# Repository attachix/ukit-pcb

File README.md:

## About
This repository contains the files needed to view, modify and manufacture the Printed Circuit Boards(PCB) for the [U:Kit sensor kit](https://github.com/attachix/ukit) project.

.

## PCBs
U:Kit consists currently of 3 PCBS
* [esp-board/](esp-board/) - ESP8266 PCB.
* [base-board/](base-board/) - the main board in the kit
* [smoke-board/](smoke-board) - the board that operates with the smoke sensor

## Hardware Overview
.

## Required Software
For viewing and modifying the PCBs you will need [KiCad](http://kicad-pcb.org/) version 4.0.5 or newer.
In Ubuntu 16.04 you can install it by typing `sudo apt install kicad`.

### Optional Software
If you want to be able to see better the differences between versions you will need
* gerbv - for differences in Gerber files
* [ImageMagick](https://www.imagemagick.org) - for differences in image files
* diffpdf - for differences in PDF files
* eeplot - for differences in Schema files.

## Copyright
Copyright (c) 2016-2018, Slavey Karadzhov <slav@attachix.com>. All rights reserved.

## Authors
* Cviatko Delchev <cviatko@attachix.com> - Our hard-core hardware guru
* Slavey Karadzhov <slav@attachix.com>
* .. Contributors - See https://github.com/attachix/ukit-pcb/graphs/contributors

## License
All files in this repository are licensed under Creative Commons Non-Commercial-Share Alike 3.0 License . See the [LICENSE](LICENSE) file details. Basically it means that

### You are free to
* Share — copy and redistribute the material in any medium or format
* Adapt — remix, transform, and build upon the material

The licensor cannot revoke these freedoms as long as you follow the license terms.

### Under the following terms:
* Attribution — You must give appropriate credit, provide a link to the license, and indicate if changes were made. You may do so in any reasonable manner, but not in any way that suggests the licensor endorses you or your use.

* NonCommercial — You may not use the material for commercial purposes.

No additional restrictions — You may not apply legal terms or technological measures that legally restrict others from doing anything the license permits.

Credit can be attributed through a link to the creator website: https://attachix.com

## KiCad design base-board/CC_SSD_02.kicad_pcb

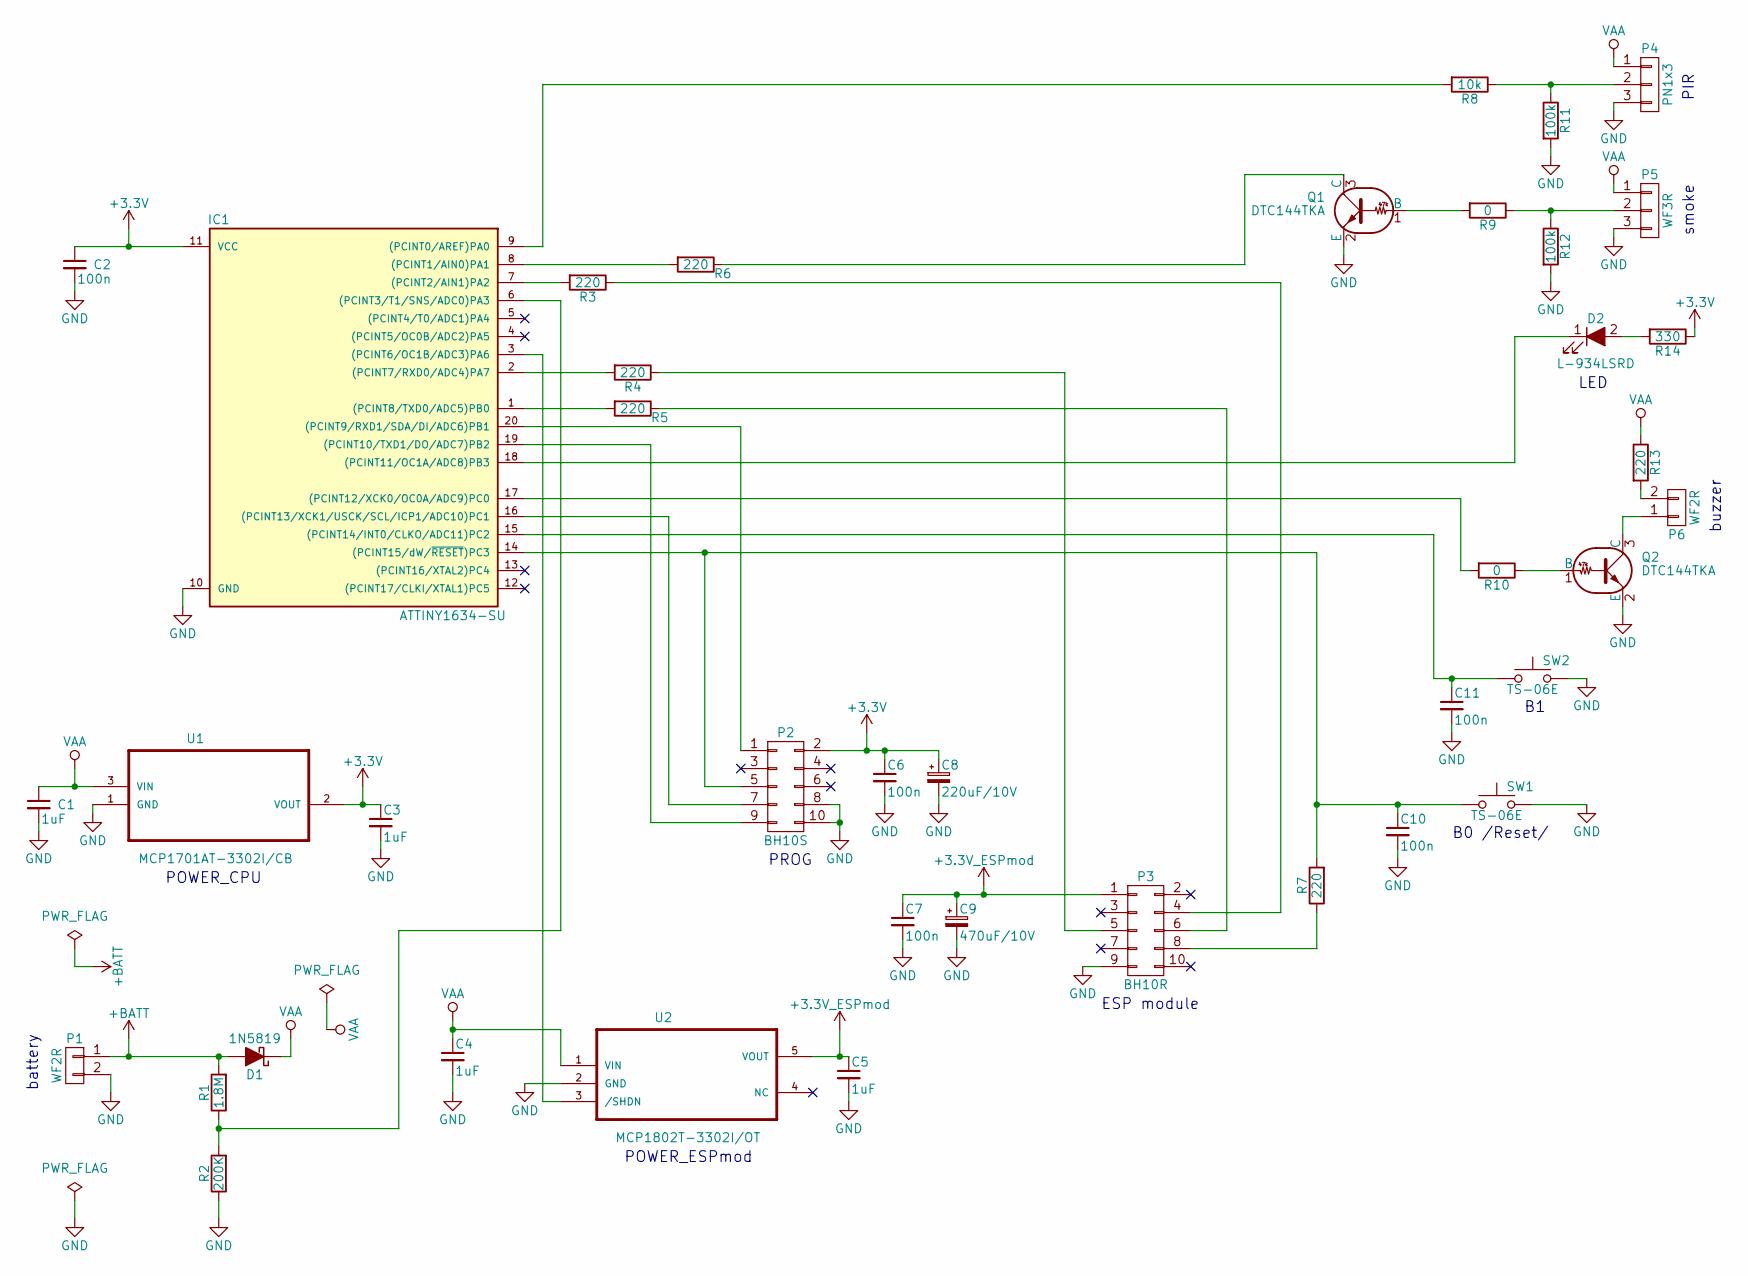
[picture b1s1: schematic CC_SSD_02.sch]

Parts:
C1, C3, C4, C5: 1uF; C_0805_HandSoldering
C2, C6, C7, C10, C11: 100n; C_0805_HandSoldering
C8: 220uF/10V; CP_Radial_D8.0mm_P2.50mm
C9: 470uF/10V; CP_Radial_D8.0mm_P2.50mm
D1: 1N5819; D_SMA_Handsoldering
D2: L-934LSRD; LED_D3.0mm
IC1: ATTINY1634-SU; SOIC-20W_7.5x12.8mm_Pitch1.27mm
P1, P6: WF2R
P2: BH10S; IDC_Header_Straight_10pins
P3: BH10R
P4: PN1x3
P5: WF3R
Q1, Q2: DTC144TKA; SOT-23_Handsoldering
R1: 1.8M; R_0805_HandSoldering
R2: 200K; R_0805_HandSoldering
R3, R4, R5, R6, R7, R13: 220; R_0805_HandSoldering
R8: 10k; R_0805_HandSoldering
R9, R10: 0; R_0805_HandSoldering
R11, R12: 100k; R_0805_HandSoldering
R14: 330; R_0805_HandSoldering
SW1, SW2: TS-06E; SW_PUSH_6mm
U1: MCP1701AT-3302I/CB; SOT-23_Handsoldering
U2: MCP1802T-3302I/OT; SOT-23-5_HandSoldering

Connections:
+3.3V_ESPmod: C5.1, C7.1, C9.1, P3.1, U2.5 (VOUT)
+3V3: C2.1, C3.1, C6.1, C8.1, IC1.11 (VCC), P2.2, R14.1, U1.2 (VOUT)
+BATT: D1.2 (A), P1.1, R1.2
GND: C1.2, C2.2, C3.2, C4.2, C5.2, C6.2, C7.2, C8.2, C9.2, C10.2, C11.2, IC1.10 (GND), P1.2, P2.8, P2.10, P3.9, P4.3, P5.3, Q1.2 (E), Q2.2 (E), R2.1, R11.2, R12.2, SW1.2, SW2.2, U1.1 (GND), U2.2 (GND)
unnamed: C10.1, IC1.14 ((PCINT15/dW/~RESET~)PC3), P2.5, R7.2, SW1.1
unnamed: C11.1, IC1.15 ((PCINT14/INT0/CLKO/ADC11)PC2), SW2.1
unnamed: D2.1 (K), IC1.18 ((PCINT11/OC1A/ADC8)PB3)
unnamed: D2.2 (A), R14.2
unnamed: IC1.1 ((PCINT8/TXD0/ADC5)PB0), R5.2
unnamed: IC1.2 ((PCINT7/RXD0/ADC4)PA7), R4.2
unnamed: IC1.3 ((PCINT6/OC1B/ADC3)PA6), U2.3 (/SHDN)
unnamed: IC1.6 ((PCINT3/T1/SNS/ADC0)PA3), R1.1, R2.2
unnamed: IC1.7 ((PCINT2/AIN1)PA2), R3.2
unnamed: IC1.8 ((PCINT1/AIN0)PA1), R6.2
unnamed: IC1.9 ((PCINT0/AREF)PA0), R8.2
unnamed: IC1.16 ((PCINT13/XCK1/USCK/SCL/ICP1/ADC10)PC1), P2.7
unnamed: IC1.17 ((PCINT12/XCK0/OC0A/ADC9)PC0), R10.2
unnamed: IC1.19 ((PCINT10/TXD1/DO/ADC7)PB2), P2.9
unnamed: IC1.20 ((PCINT9/RXD1/SDA/DI/ADC6)PB1), P2.1
unnamed: P3.4, R3.1
unnamed: P3.5, R4.1
unnamed: P3.6, R5.1
unnamed: P3.8, R7.1
unnamed: P4.2, R8.1, R11.1
unnamed: P5.2, R9.1, R12.1
unnamed: P6.1, Q2.3 (C)
unnamed: P6.2, R13.2
unnamed: Q1.1 (B), R9.2
unnamed: Q1.3 (C), R6.1
unnamed: Q2.1 (B), R10.1
VAA: C1.1, C4.1, D1.1 (K), P4.1, P5.1, R13.1, U1.3 (VIN), U2.1 (VIN)

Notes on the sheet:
PROG
ESP module
B0 /Reset/
buzzer
smoke
battery
PIR
LED
POWER_CPU
POWER_ESPmod

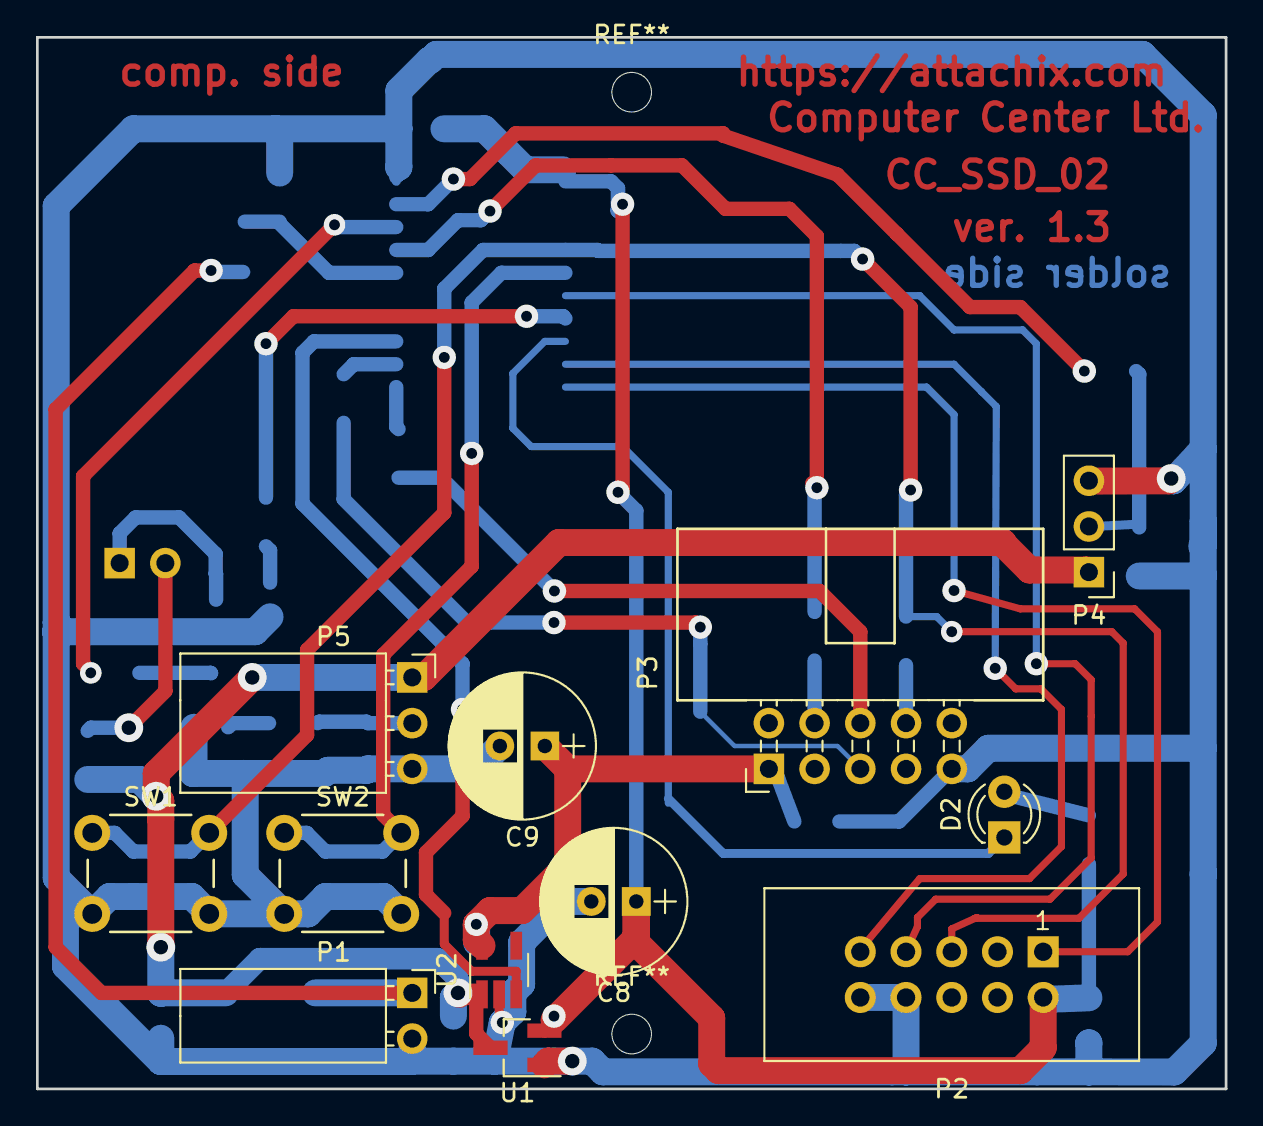
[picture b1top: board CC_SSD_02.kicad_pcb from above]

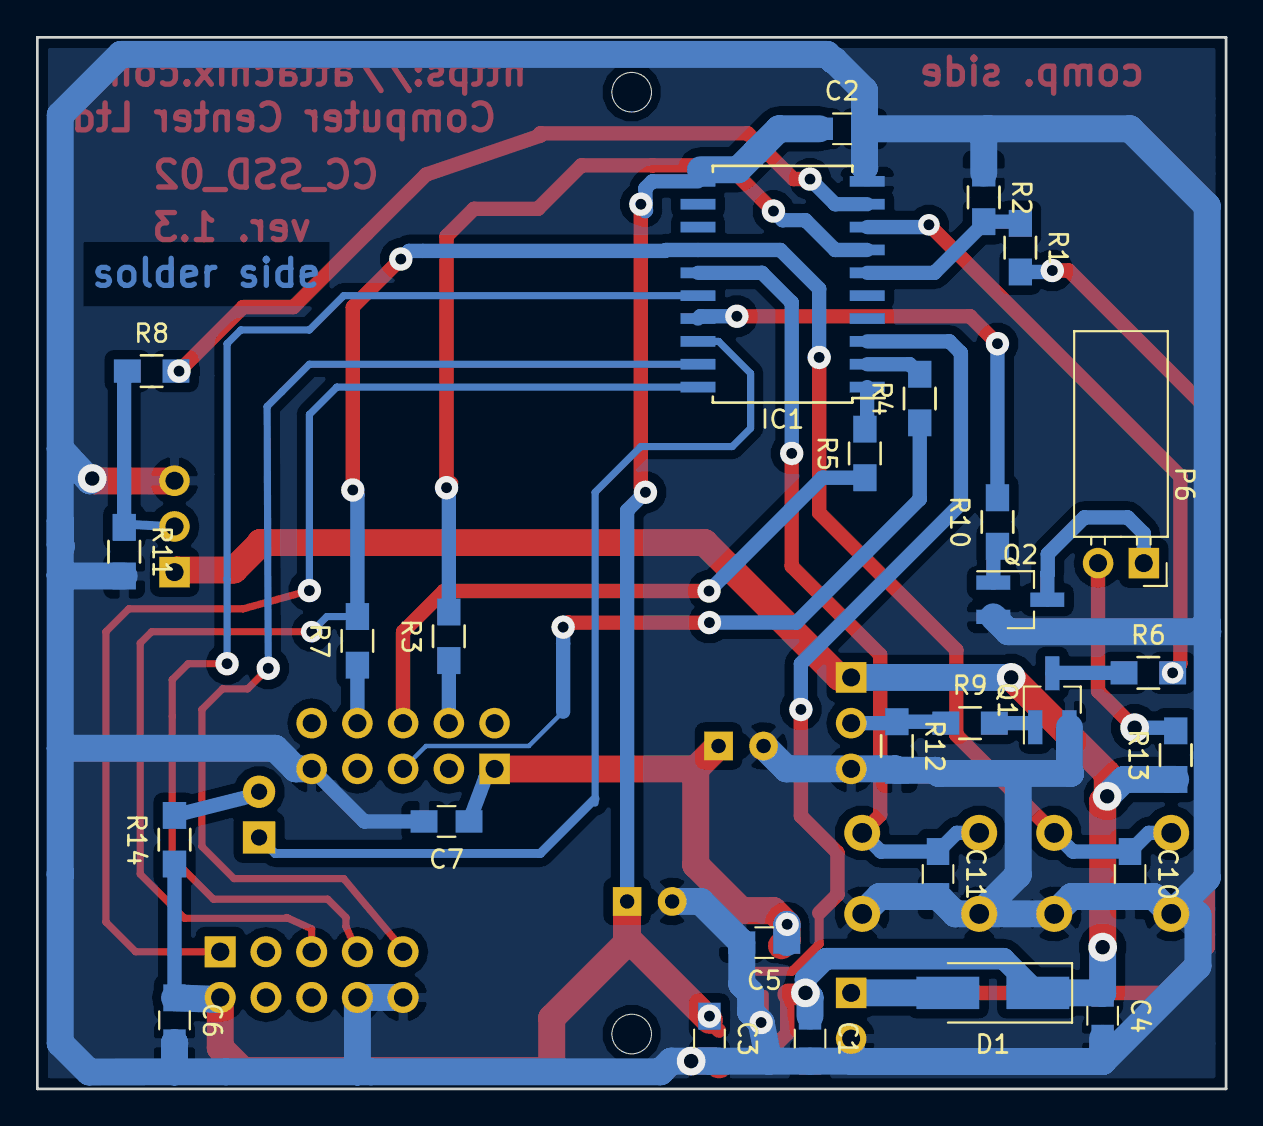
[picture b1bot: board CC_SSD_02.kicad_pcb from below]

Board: 2 copper layers, 66.0 x 58.4 mm, 40 parts (28 on the bottom side), 31 nets.

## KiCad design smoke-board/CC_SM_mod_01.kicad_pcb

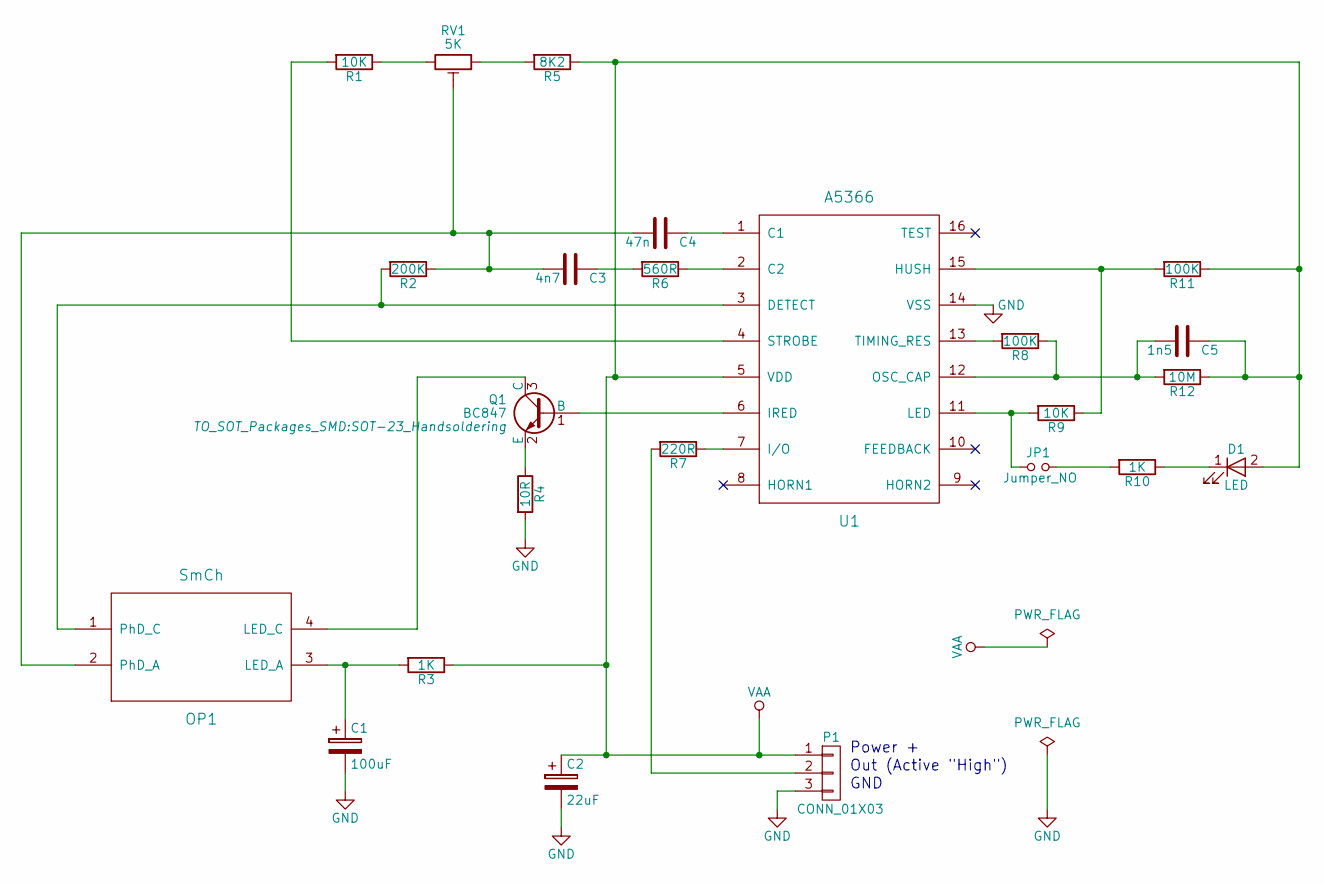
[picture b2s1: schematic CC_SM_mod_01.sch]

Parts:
C1: 100uF; CP_Radial_D6.3mm_P2.50mm
C2: 22uF; CP_Radial_D4.0mm_P2.00mm
C3: 4n7; C_0805_HandSoldering
C4: 47n; C_0805_HandSoldering; mouser# 710-885012207043
C5: 1n5; C_0805_HandSoldering
D1: LED; LED_D3.0mm
JP1: Jumper_NO; Pin_Header_Straight_1x02_Pitch2.54mm
OP1: SmCh; SmCh_LS-512-2
P1: CONN_01X03; WF3R
Q1: BC847; SOT-23_Handsoldering
R1, R9: 10K; R_0805_HandSoldering
R2: 200K; R_0805_HandSoldering
R3, R10: 1K; R_0805_HandSoldering
R4: 10R; R_0805_HandSoldering
R5: 8K2; R_0805_HandSoldering
R6: 560R; R_0805_HandSoldering
R7: 220R; R_0805_HandSoldering
R8, R11: 100K; R_0805_HandSoldering
R12: 10M; R_0805_HandSoldering
RV1: 5K; Potentiometer_Trimmer_Piher_PT-6v_Horizontal
U1: A5366; DIP-16_W7.62mm_Socket

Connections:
GND: C1.2, C2.2, P1.3, R4.2, U1.14 (VSS)
unnamed: C1.1, OP1.3 (LED_A), R3.2
unnamed: C3.1, R6.2
unnamed: C3.2, C4.2, OP1.2 (PhD_A), R2.1, RV1.2
unnamed: C4.1, U1.1 (C1)
unnamed: C5.2, R8.1, R12.2, U1.12 (OSC_CAP)
unnamed: D1.1 (K), R10.1
unnamed: JP1.1, R9.2, U1.11 (LED)
unnamed: JP1.2, R10.2
unnamed: OP1.1 (PhD_C), R2.2, U1.3 (DETECT)
unnamed: OP1.4 (LED_C), Q1.3 (C)
unnamed: P1.2, R7.2
unnamed: Q1.1 (B), U1.6 (IRED)
unnamed: Q1.2 (E), R4.1
unnamed: R1.1, RV1.3
unnamed: R1.2, U1.4 (STROBE)
unnamed: R5.2, RV1.1
unnamed: R6.1, U1.2 (C2)
unnamed: R7.1, U1.7 (I/O)
unnamed: R8.2, U1.13 (TIMING_RES)
unnamed: R9.1, R11.2, U1.15 (HUSH)
VAA: C2.1, C5.1, D1.2 (A), P1.1, R3.1, R5.1, R11.1, R12.1, U1.5 (VDD)

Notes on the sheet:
Power +
Out (Active "High")
GND

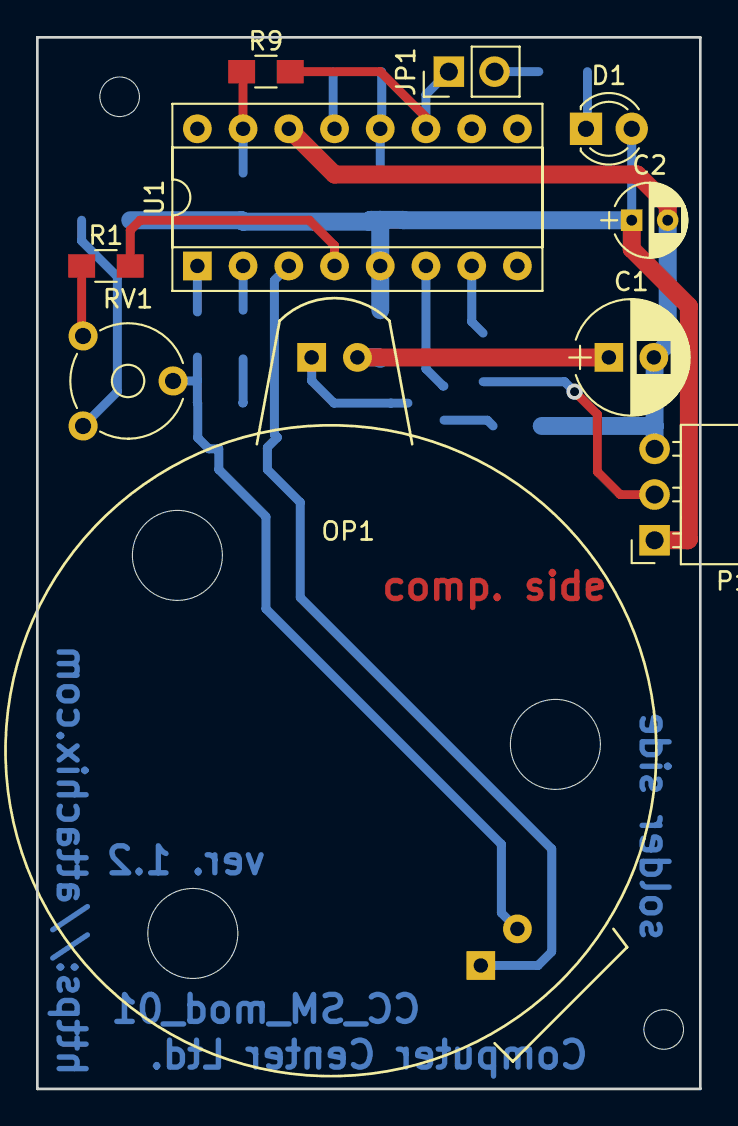
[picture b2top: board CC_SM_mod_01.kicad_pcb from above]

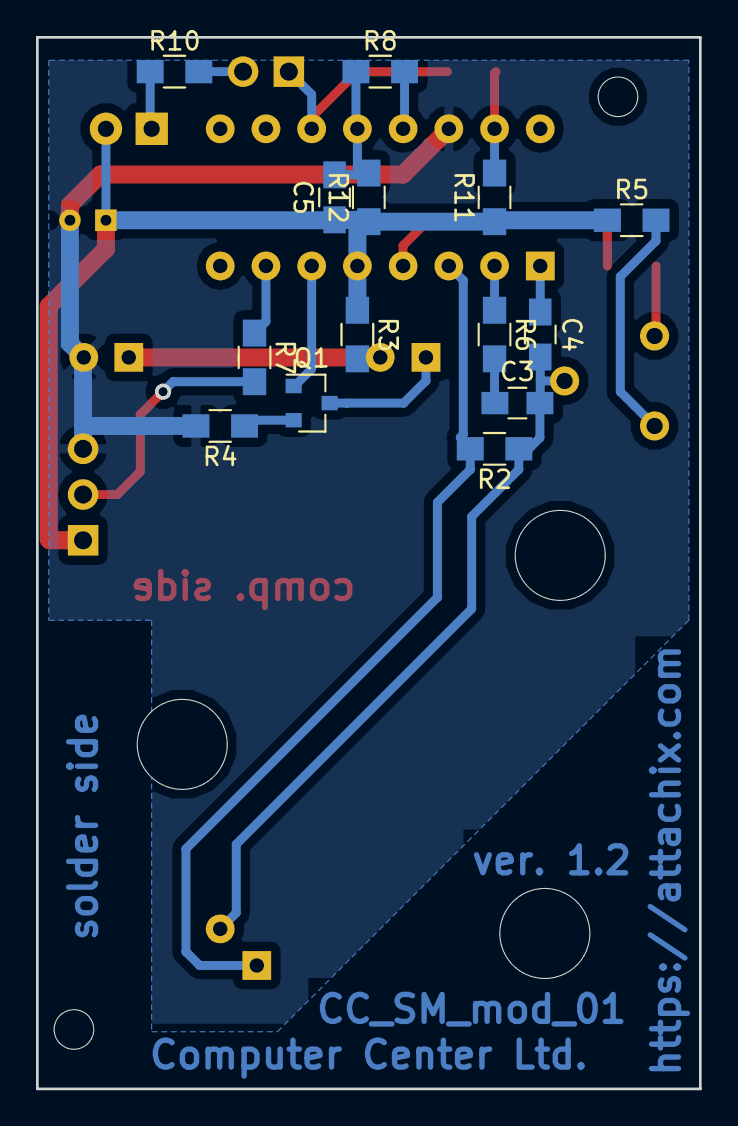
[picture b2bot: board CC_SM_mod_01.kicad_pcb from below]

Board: 2 copper layers, 36.8 x 58.4 mm, 24 parts (14 on the bottom side), 22 nets.

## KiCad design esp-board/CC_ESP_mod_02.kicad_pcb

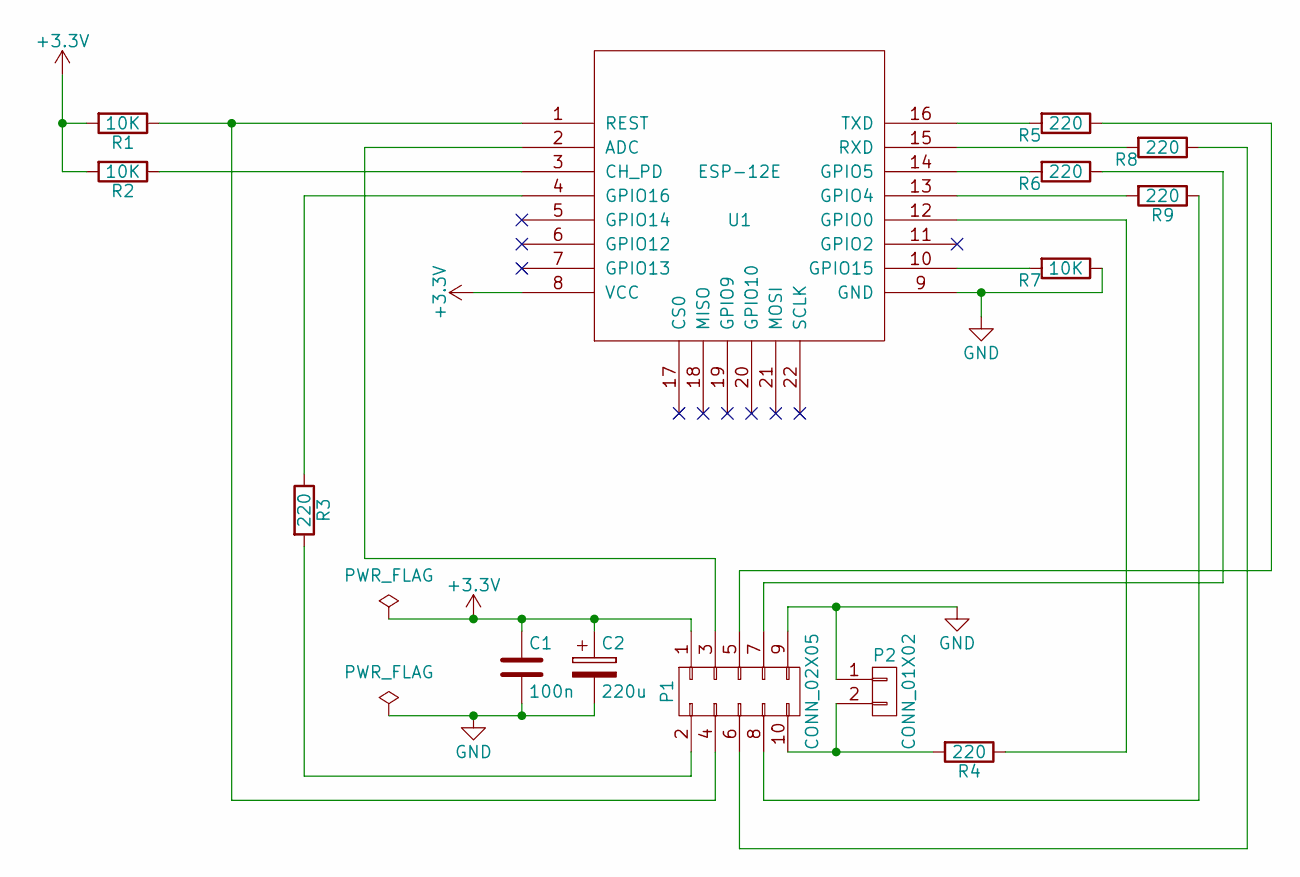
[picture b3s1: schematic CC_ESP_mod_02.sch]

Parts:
C1: 100n; C_0805_HandSoldering
C2: 220u; CP_Radial_D6.3mm_P2.50mm
P1: CONN_02X05; Socket_Strip_Angled_2x05
P2: CONN_01X02; Socket_Strip_Straight_1x02
R1, R2, R7: 10K; R_0805_HandSoldering
R3, R4, R5, R6, R8, R9: 220; R_0805_HandSoldering
U1: ESP-12E

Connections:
+3V3: C1.1, C2.1, P1.1, R1.2, R2.2, U1.8 (VCC)
GND: C1.2, C2.2, P1.9, P2.1, R7.1, U1.9 (GND)
unnamed: P1.2, R3.2
unnamed: P1.3, U1.2 (ADC)
unnamed: P1.4, R1.1, U1.1 (REST)
unnamed: P1.5, R5.1
unnamed: P1.6, R8.1
unnamed: P1.7, R6.1
unnamed: P1.8, R9.1
unnamed: P1.10, P2.2, R4.2
unnamed: R2.1, U1.3 (CH_PD)
unnamed: R3.1, U1.4 (GPIO16)
unnamed: R4.1, U1.12 (GPIO0)
unnamed: R5.2, U1.16 (TXD)
unnamed: R6.2, U1.14 (GPIO5)
unnamed: R7.2, U1.10 (GPIO15)
unnamed: R8.2, U1.15 (RXD)
unnamed: R9.2, U1.13 (GPIO4)

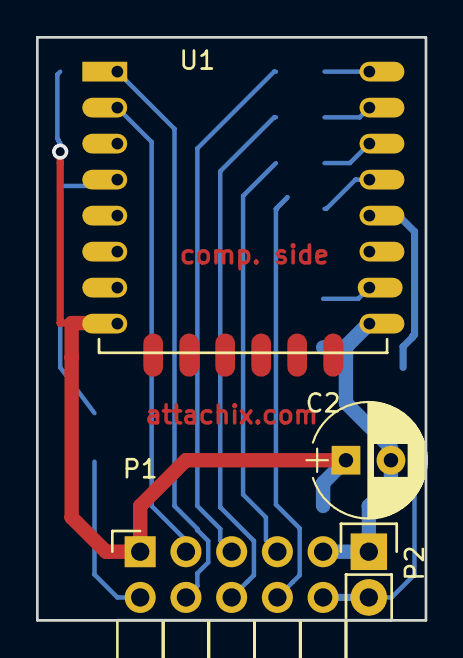
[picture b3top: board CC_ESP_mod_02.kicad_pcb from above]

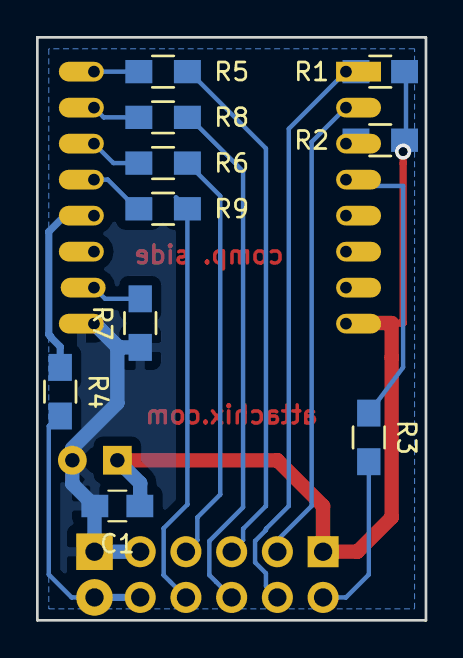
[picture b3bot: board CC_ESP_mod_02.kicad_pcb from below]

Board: 2 copper layers, 21.6 x 32.4 mm, 14 parts (10 on the bottom side), 18 nets.

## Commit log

2018-04-15 Preparation ...
2018-04-17 Initial public version of the ESP8266-board.
2018-05-18 Added the base-board and the smoke-board. All PCBs needed to build the device are not present.
2018-05-18 Added automation.
2018-10-01 Moved smoke detector header more to the center. Reverted header for Attiny programmer to be straight.
2019-01-23 Slightly moved the holes so that the smoke PCB does not push the walls of the enclosure.
2019-01-24 Added new version of the base board with fixes for the connectors and LED moved closer to the ring.
